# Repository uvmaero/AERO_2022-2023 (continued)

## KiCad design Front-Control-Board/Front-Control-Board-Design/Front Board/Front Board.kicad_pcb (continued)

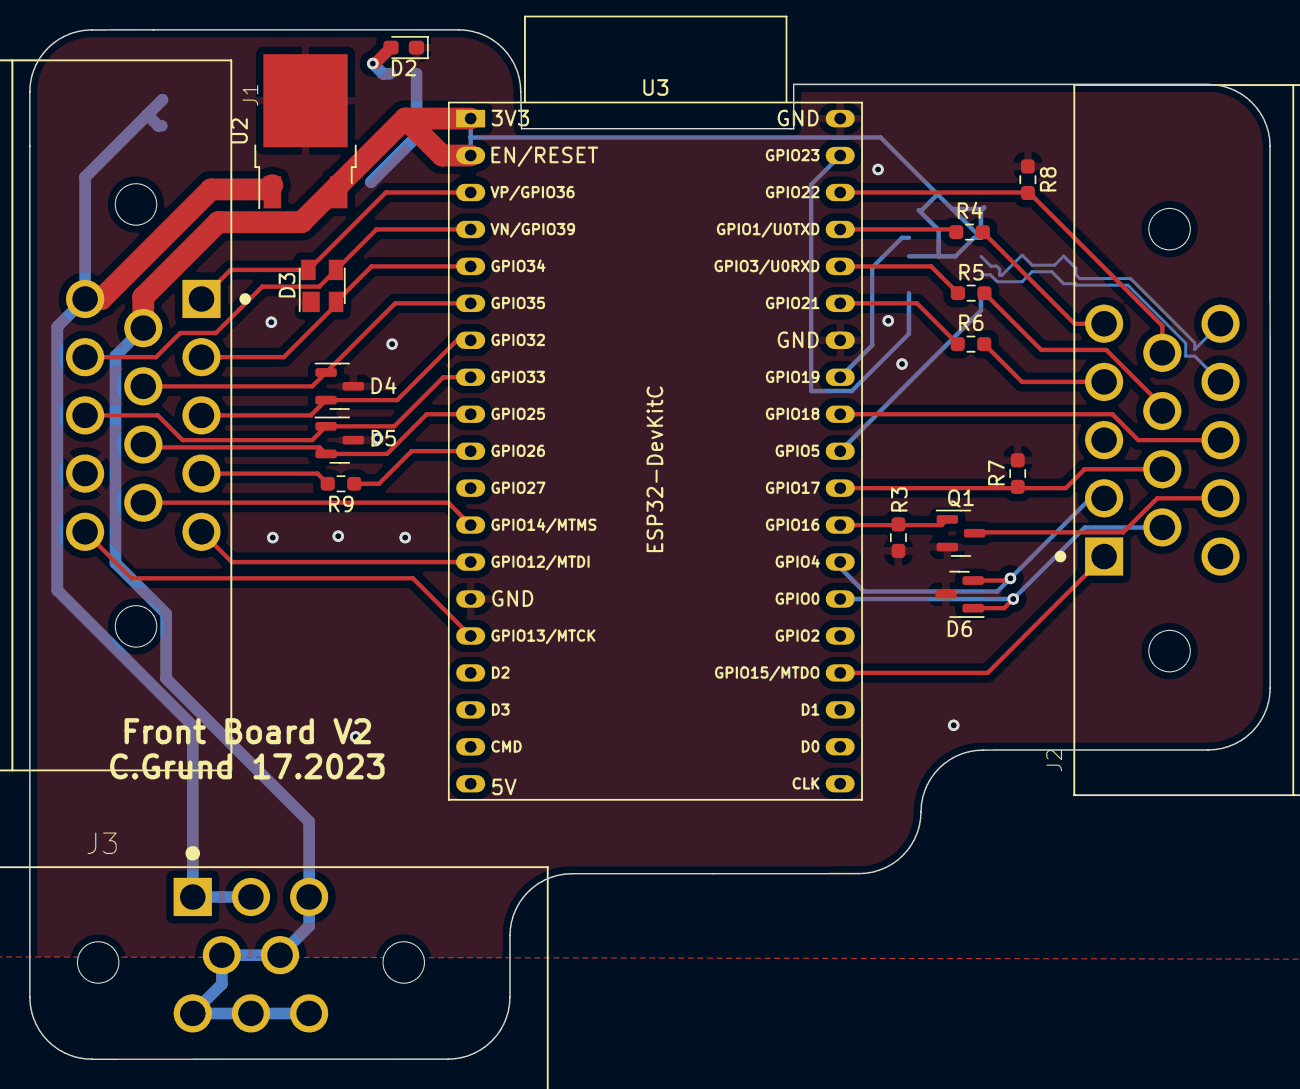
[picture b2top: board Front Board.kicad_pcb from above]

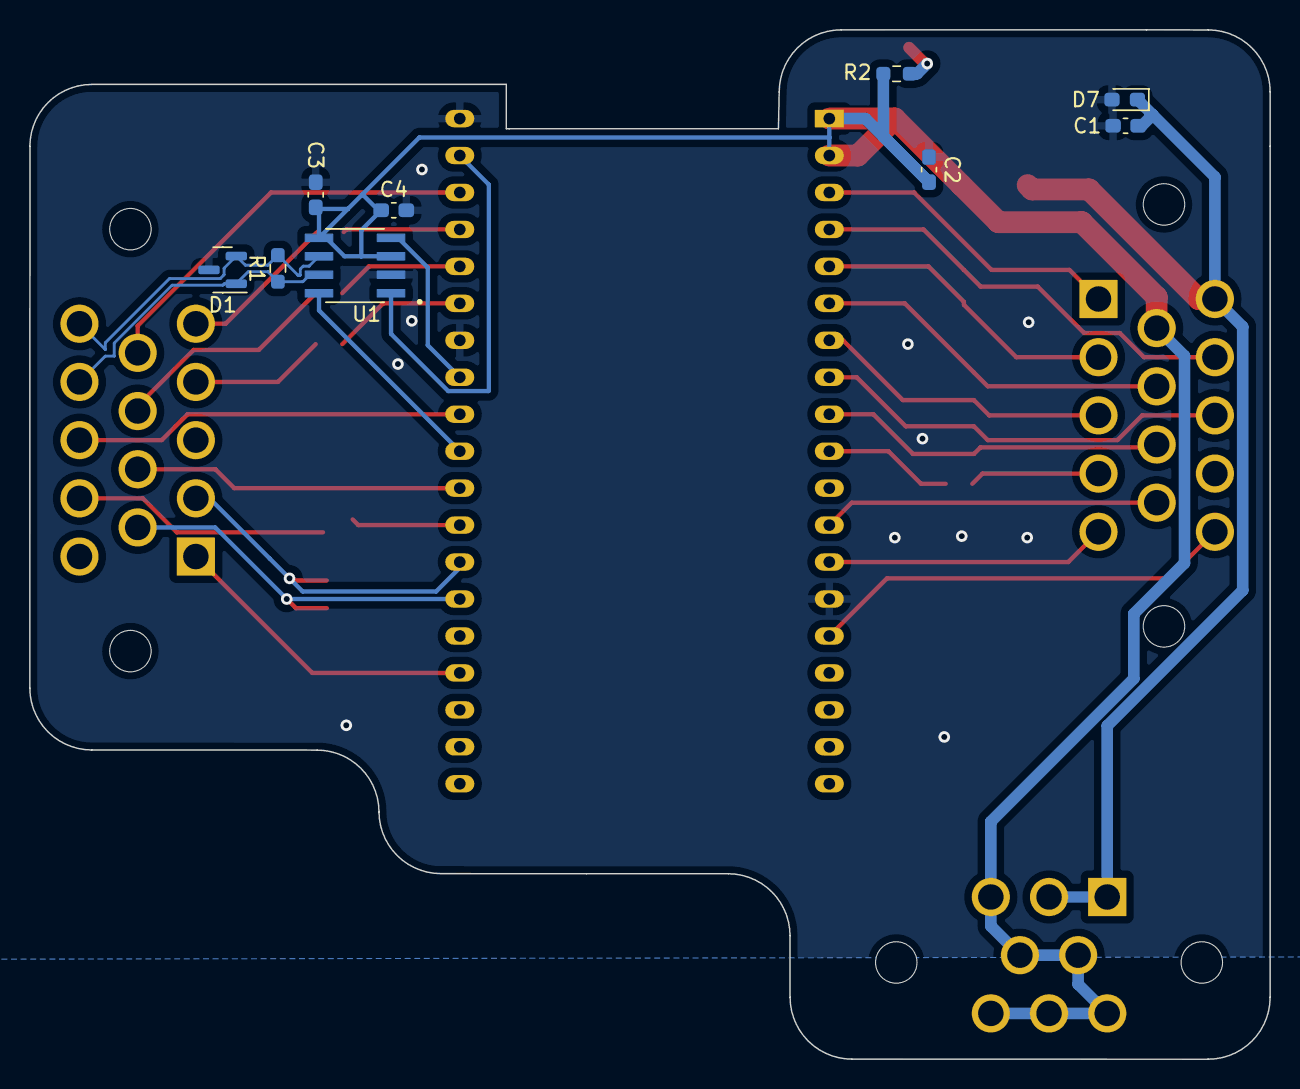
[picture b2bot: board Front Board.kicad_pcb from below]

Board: 2 copper layers, 85.2 x 70.7 mm, 27 parts (9 on the bottom side), 34 nets.

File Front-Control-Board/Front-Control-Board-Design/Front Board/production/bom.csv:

Designator,Footprint,Quantity,Value,LCSC Part #
C1,0603,1,10uF,
C2,0603,1,10uF,
C3,0603,1,0.1u,
C4,0603,1,0.1u,
D1,SOT-23,1,DESD2CAN2SOQ-7,
D2,0603,1,LED,
D3,SOT-143,1,SP0503BAHT,
"D4, D5, D6",SOT-23,3,SP0502BAHT,
D7,0603,1,TS4148C RZG,
"J1, J2",TE_1-776266-1_14pin_Horizontal,2,Conn_01x14,
J3,TE_1-776280-1_8pin_Horizontal,1,Conn_01x08,
Q1,SOT-23,1,2N7002,
R1,0603,1,120,
R2,0603,1,330,
R3,0603,1,10k,
R4,0603,1,100,
R5,0603,1,100,
R6,0603,1,100,
R7,0603,1,10k,
R8,0603,1,10k,
R9,0603,1,100,
U1,SOIC127P600X175-8N,1,MAX33054EASA+T,
U2,TO-252-2,1,TS2940CP33_ROG,
U3,ESP32-DevKitC,1,ESP32-DevKitC,

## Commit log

2022-11-11 First commit to back up
2022-11-30 Pins
    Added pinmodes
    Added brake light control
    Added json creation
2023-02-06 oops forgot to push for awile
2023-02-07 charger schematic
2023-02-21 push
2023-02-21 bat pac
2023-02-21 documentation
2023-02-28 tracktive
2023-03-06 removed code
2023-03-31 OOPSIE
2023-05-15 end of year DUMP
